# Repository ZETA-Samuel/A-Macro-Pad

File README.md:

# A-Macro-Pad
This repo contains simple, yet, useful macro pad that is easy to integate in daily life!

Also, Download scottokeebs footprint from Github and import it.

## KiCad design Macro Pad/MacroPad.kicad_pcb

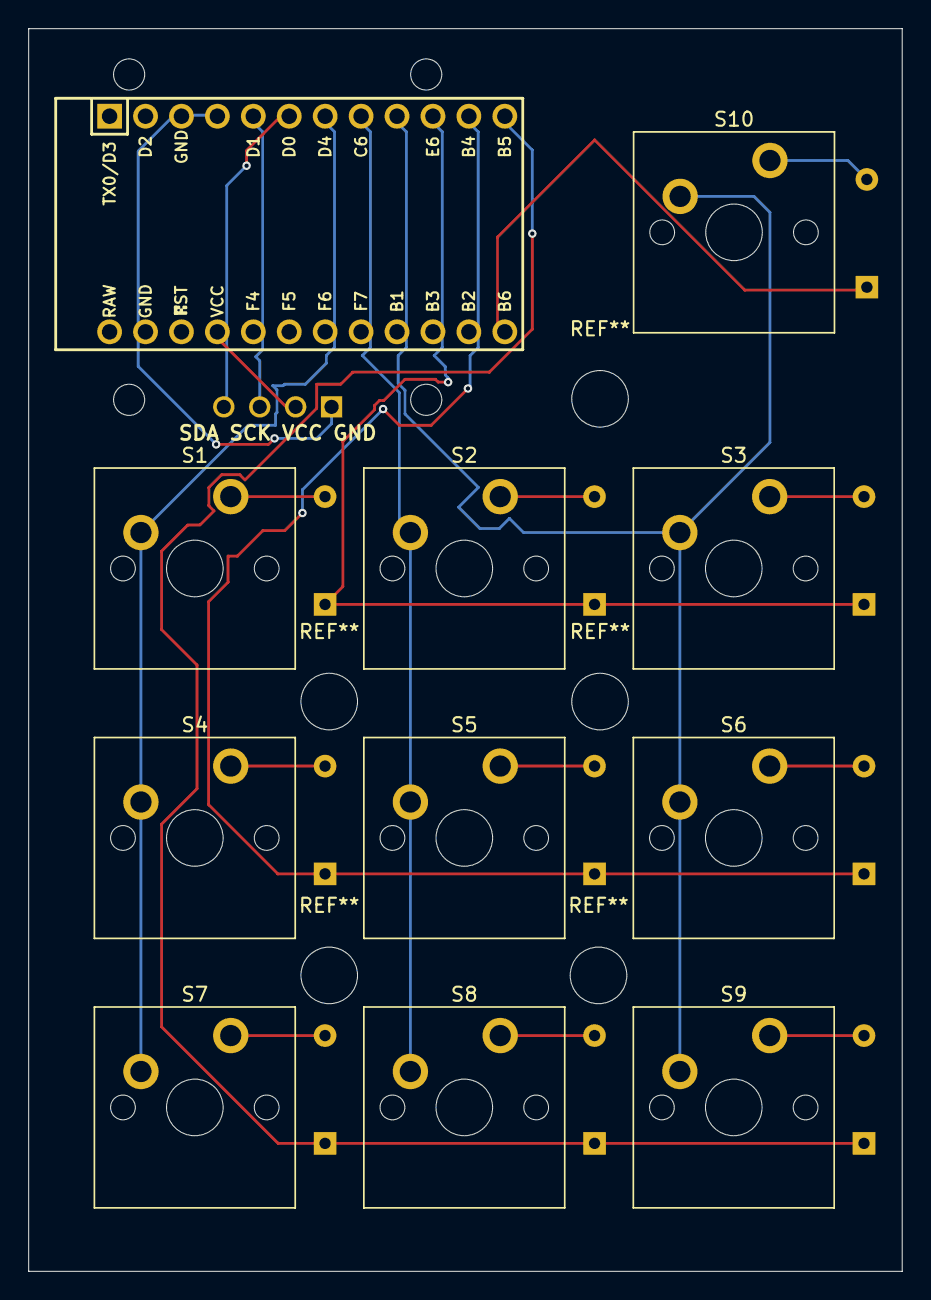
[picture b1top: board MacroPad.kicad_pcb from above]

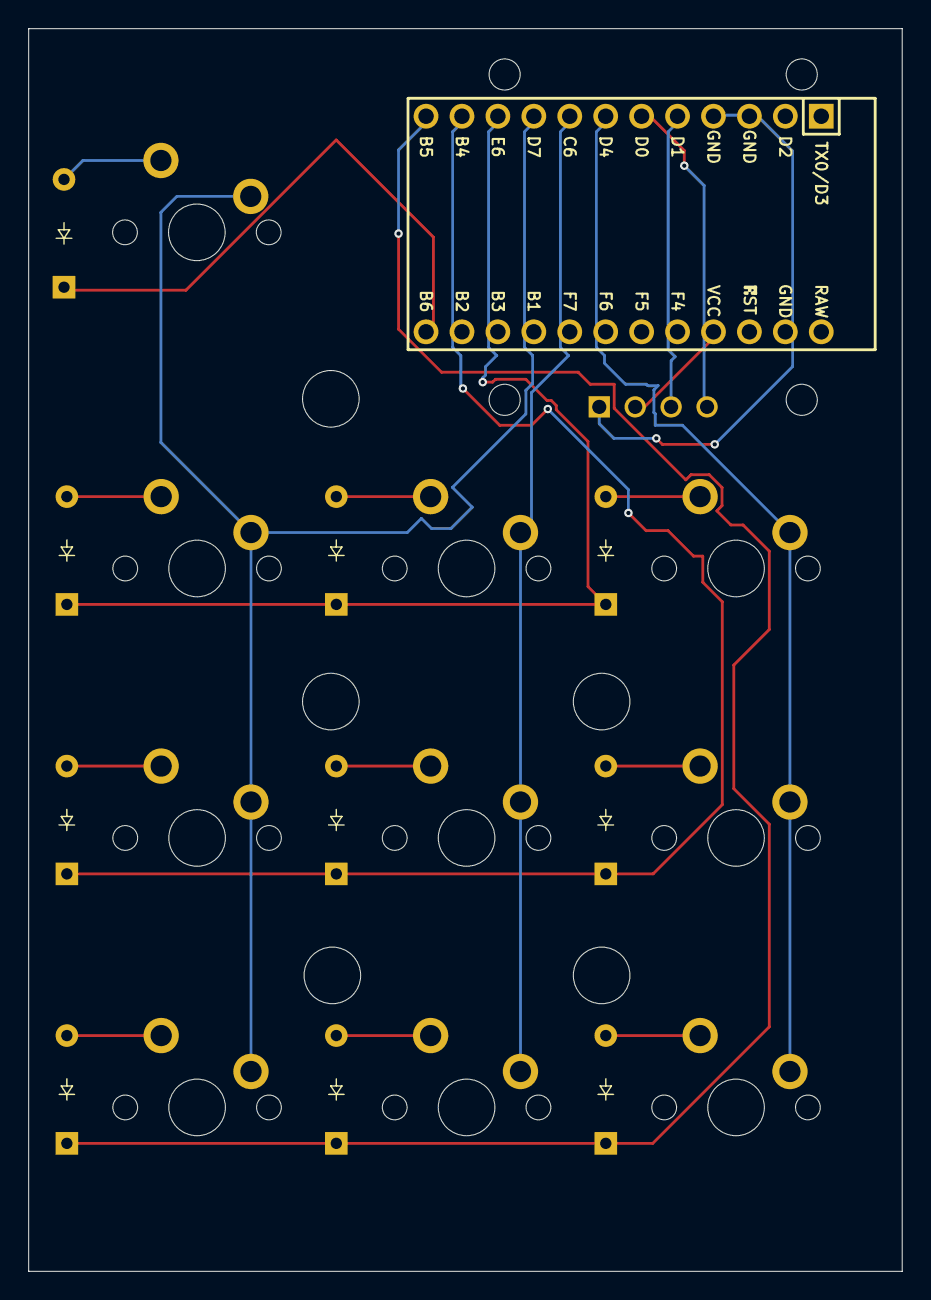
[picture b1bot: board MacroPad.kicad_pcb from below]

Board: 2 copper layers, 61.8 x 87.9 mm, 22 parts (11 on the bottom side), 16 nets.

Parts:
D1, D2, D3, D4, D5, D6, D7, D8, D9, D10: Diode_DO-35
J2: OLED_128x64
S1, S2, S3, S4, S5, S6, S7, S8, S9, S10: MX_PCB_1.00u
U1: Arduino_Pro_Micro

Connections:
Col 0: S1.1, S4.1, S7.1
Col 1: S2.1, S5.1, S8.1
Col 2: S3.1, S6.1, S9.1, S10.1
unnamed: D1.2 (A), S1.2
unnamed: D2.2 (A), S2.2
unnamed: D3.2 (A), S3.2
unnamed: D4.2 (A), S4.2
unnamed: D5.2 (A), S5.2
unnamed: D6.2 (A), S6.2
unnamed: D7.2 (A), S7.2
unnamed: D8.2 (A), S8.2
unnamed: D9.2 (A), S9.2
unnamed: D10.2 (A), S10.2
Row 0: D1.1 (K), D2.1 (K), D3.1 (K)
Row 1: D4.1 (K), D5.1 (K), D6.1 (K)
Row 2: D7.1 (K), D8.1 (K), D9.1 (K)

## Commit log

2026-06-14 commited
2026-06-14 Remove lock file
2026-06-25 All required files!
